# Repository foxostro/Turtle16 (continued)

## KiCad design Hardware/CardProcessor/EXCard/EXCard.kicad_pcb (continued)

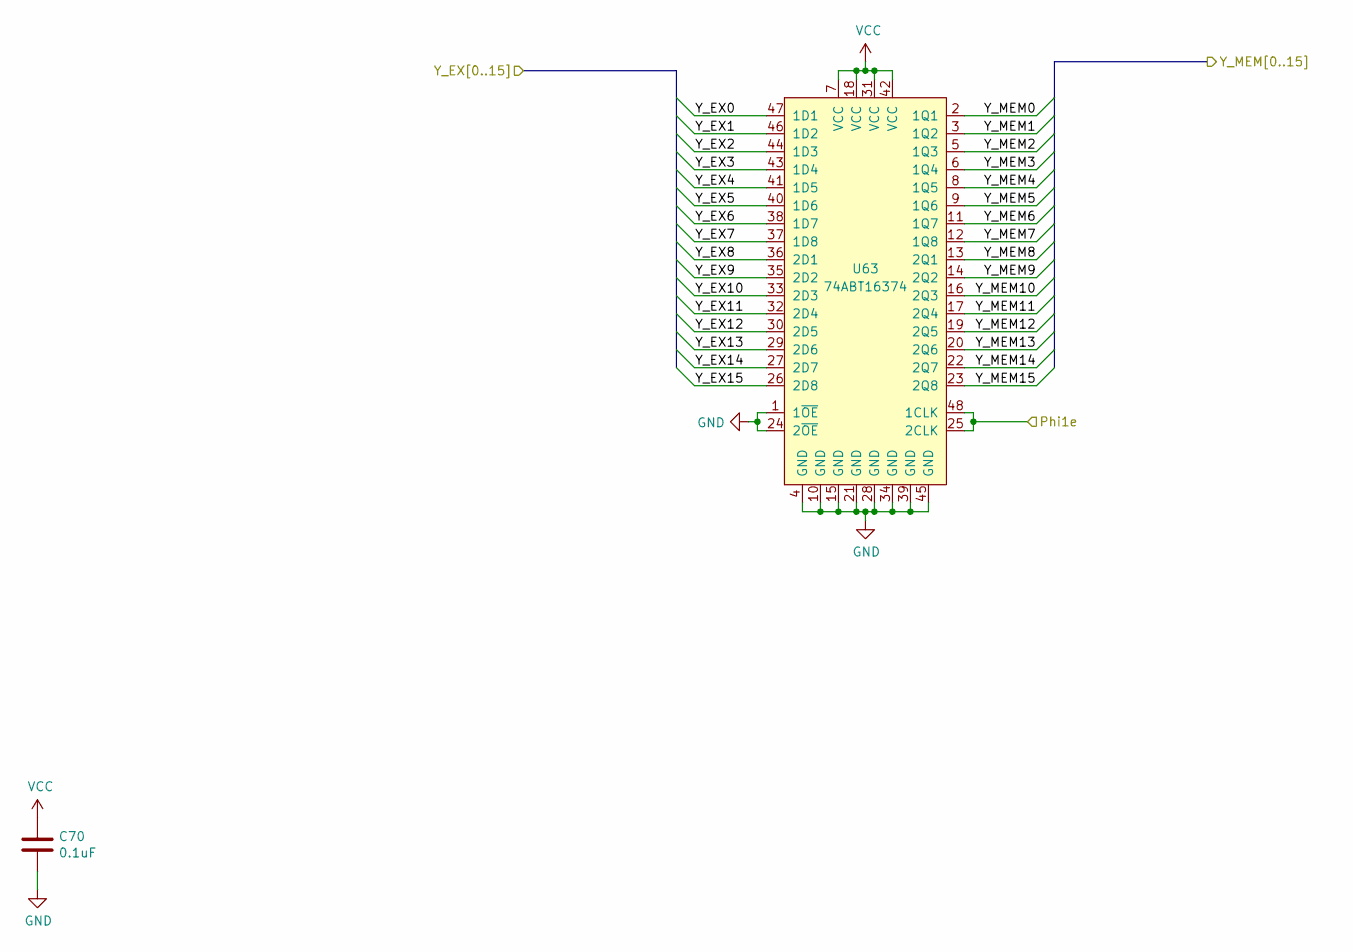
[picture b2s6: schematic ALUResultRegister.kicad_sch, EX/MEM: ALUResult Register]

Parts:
C70: 0.1uF; C_0603_1608Metric; Manufacturer# EMK107B7104KAHT; Digikey# 587-6004-1-ND
U63: 74ABT16374; TSSOP-48_6.1x12.5mm_P0.5mm; Manufacturer# SN74ABT16374ADGGR; Mouser# 595-SNABT16374ADGGR

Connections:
/Phi1e: U63.25 (2CLK), U63.48 (1CLK); also elsewhere on the board
/Y_EX0: U63.47 (1D1); also elsewhere on the board
/Y_EX1: U63.46 (1D2); also elsewhere on the board
/Y_EX2: U63.44 (1D3); also elsewhere on the board
/Y_EX3: U63.43 (1D4); also elsewhere on the board
/Y_EX4: U63.41 (1D5); also elsewhere on the board
/Y_EX5: U63.40 (1D6); also elsewhere on the board
/Y_EX6: U63.38 (1D7); also elsewhere on the board
/Y_EX7: U63.37 (1D8); also elsewhere on the board
/Y_EX8: U63.36 (2D1); also elsewhere on the board
/Y_EX9: U63.35 (2D2); also elsewhere on the board
/Y_EX10: U63.33 (2D3); also elsewhere on the board
/Y_EX11: U63.32 (2D4); also elsewhere on the board
/Y_EX12: U63.30 (2D5); also elsewhere on the board
/Y_EX13: U63.29 (2D6); also elsewhere on the board
/Y_EX14: U63.27 (2D7); also elsewhere on the board
/Y_EX15: U63.26 (2D8); also elsewhere on the board
/Y_MEM0: U63.2 (1Q1); also elsewhere on the board
/Y_MEM1: U63.3 (1Q2); also elsewhere on the board
/Y_MEM2: U63.5 (1Q3); also elsewhere on the board
/Y_MEM3: U63.6 (1Q4); also elsewhere on the board
/Y_MEM4: U63.8 (1Q5); also elsewhere on the board
/Y_MEM5: U63.9 (1Q6); also elsewhere on the board
/Y_MEM6: U63.11 (1Q7); also elsewhere on the board
/Y_MEM7: U63.12 (1Q8); also elsewhere on the board
/Y_MEM8: U63.13 (2Q1); also elsewhere on the board
/Y_MEM9: U63.14 (2Q2); also elsewhere on the board
/Y_MEM10: U63.16 (2Q3); also elsewhere on the board
/Y_MEM11: U63.17 (2Q4); also elsewhere on the board
/Y_MEM12: U63.19 (2Q5); also elsewhere on the board
/Y_MEM13: U63.20 (2Q6); also elsewhere on the board
/Y_MEM14: U63.22 (2Q7); also elsewhere on the board
/Y_MEM15: U63.23 (2Q8); also elsewhere on the board
GND: C70.2, U63.1 (1~OE), U63.4 (GND), U63.10 (GND), U63.15 (GND), U63.21 (GND), U63.24 (2~OE), U63.28 (GND), U63.34 (GND), U63.39 (GND), U63.45 (GND); also elsewhere on the board
VCC: C70.1, U63.7 (VCC), U63.18 (VCC), U63.31 (VCC), U63.42 (VCC); also elsewhere on the board

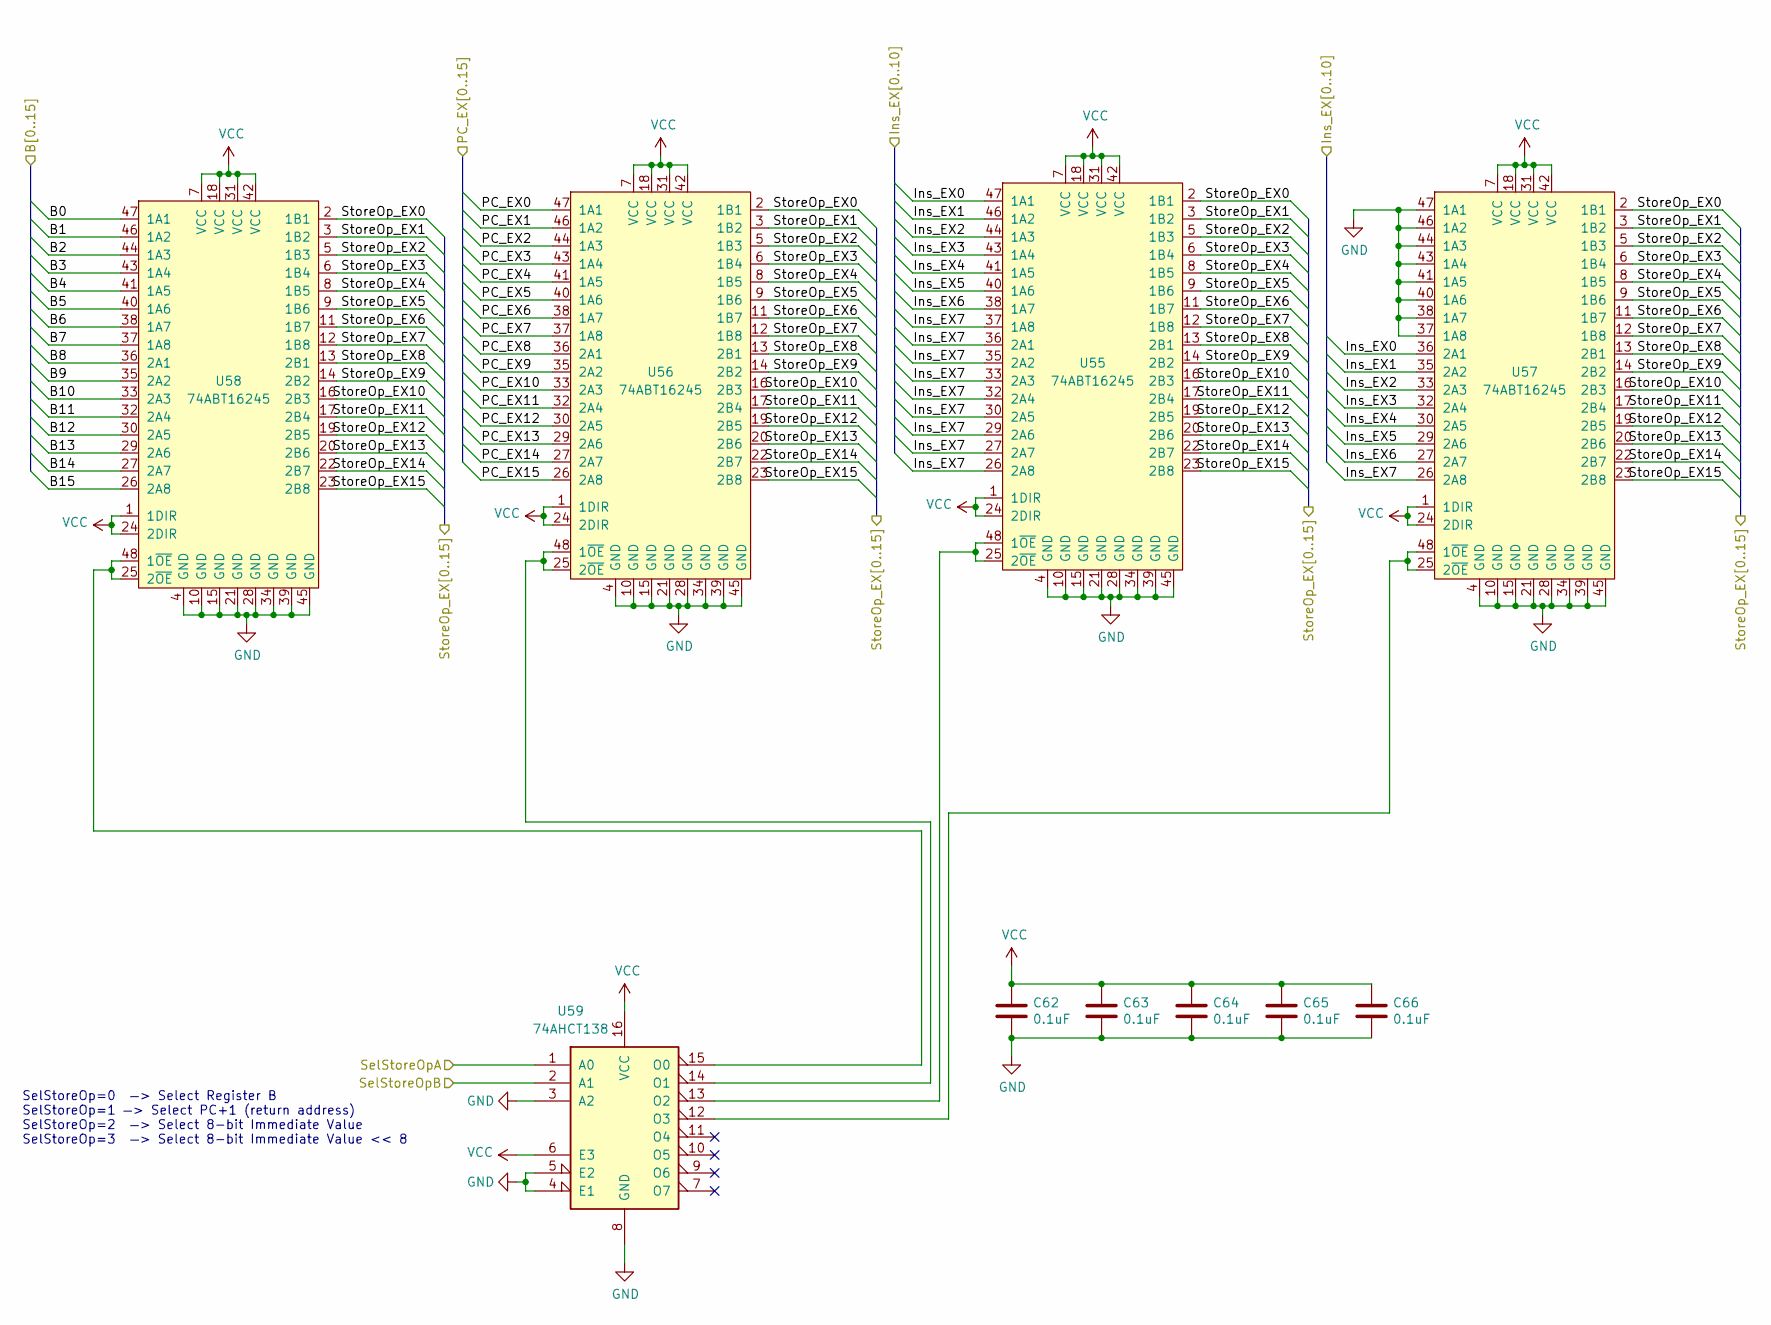
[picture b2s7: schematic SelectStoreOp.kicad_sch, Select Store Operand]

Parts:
C62, C63, C64, C65, C66: 0.1uF; C_0603_1608Metric; Manufacturer# EMK107B7104KAHT; Mouser# 963-EMK107B7104KAHT
U55, U56, U57, U58: 74ABT16245; TSSOP-48_6.1x12.5mm_P0.5mm; Manufacturer# SN74ABTH16245DGGR; Mouser# 595-SNABTH16245DGGR
U59: 74AHCT138; TSSOP-16_4.4x5mm_P0.65mm; Manufacturer# SN74AHCT138PWR; Mouser# 595-SN74AHCT138PWR

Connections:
/B0: U58.47 (1A1); also elsewhere on the board
/B1: U58.46 (1A2); also elsewhere on the board
/B2: U58.44 (1A3); also elsewhere on the board
/B3: U58.43 (1A4); also elsewhere on the board
/B4: U58.41 (1A5); also elsewhere on the board
/B5: U58.40 (1A6); also elsewhere on the board
/B6: U58.38 (1A7); also elsewhere on the board
/B7: U58.37 (1A8); also elsewhere on the board
/B8: U58.36 (2A1); also elsewhere on the board
/B9: U58.35 (2A2); also elsewhere on the board
/B10: U58.33 (2A3); also elsewhere on the board
/B11: U58.32 (2A4); also elsewhere on the board
/B12: U58.30 (2A5); also elsewhere on the board
/B13: U58.29 (2A6); also elsewhere on the board
/B14: U58.27 (2A7); also elsewhere on the board
/B15: U58.26 (2A8); also elsewhere on the board
/Ctl_EX1: U59.1 (A0); also elsewhere on the board
/Ctl_EX2: U59.2 (A1); also elsewhere on the board
/EX/sheet5FD8D6EA/StoreOp_EX0: U55.2 (1B1), U56.2 (1B1), U57.2 (1B1), U58.2 (1B1); also elsewhere on the board
/EX/sheet5FD8D6EA/StoreOp_EX1: U55.3 (1B2), U56.3 (1B2), U57.3 (1B2), U58.3 (1B2); also elsewhere on the board
/EX/sheet5FD8D6EA/StoreOp_EX2: U55.5 (1B3), U56.5 (1B3), U57.5 (1B3), U58.5 (1B3); also elsewhere on the board
/EX/sheet5FD8D6EA/StoreOp_EX3: U55.6 (1B4), U56.6 (1B4), U57.6 (1B4), U58.6 (1B4); also elsewhere on the board
/EX/sheet5FD8D6EA/StoreOp_EX4: U55.8 (1B5), U56.8 (1B5), U57.8 (1B5), U58.8 (1B5); also elsewhere on the board
/EX/sheet5FD8D6EA/StoreOp_EX5: U55.9 (1B6), U56.9 (1B6), U57.9 (1B6), U58.9 (1B6); also elsewhere on the board
/EX/sheet5FD8D6EA/StoreOp_EX6: U55.11 (1B7), U56.11 (1B7), U57.11 (1B7), U58.11 (1B7); also elsewhere on the board
/EX/sheet5FD8D6EA/StoreOp_EX7: U55.12 (1B8), U56.12 (1B8), U57.12 (1B8), U58.12 (1B8); also elsewhere on the board
/EX/sheet5FD8D6EA/StoreOp_EX8: U55.13 (2B1), U56.13 (2B1), U57.13 (2B1), U58.13 (2B1); also elsewhere on the board
/EX/sheet5FD8D6EA/StoreOp_EX9: U55.14 (2B2), U56.14 (2B2), U57.14 (2B2), U58.14 (2B2); also elsewhere on the board
/EX/sheet5FD8D6EA/StoreOp_EX10: U55.16 (2B3), U56.16 (2B3), U57.16 (2B3), U58.16 (2B3); also elsewhere on the board
/EX/sheet5FD8D6EA/StoreOp_EX11: U55.17 (2B4), U56.17 (2B4), U57.17 (2B4), U58.17 (2B4); also elsewhere on the board
/EX/sheet5FD8D6EA/StoreOp_EX12: U55.19 (2B5), U56.19 (2B5), U57.19 (2B5), U58.19 (2B5); also elsewhere on the board
/EX/sheet5FD8D6EA/StoreOp_EX13: U55.20 (2B6), U56.20 (2B6), U57.20 (2B6), U58.20 (2B6); also elsewhere on the board
/EX/sheet5FD8D6EA/StoreOp_EX14: U55.22 (2B7), U56.22 (2B7), U57.22 (2B7), U58.22 (2B7); also elsewhere on the board
/EX/sheet5FD8D6EA/StoreOp_EX15: U55.23 (2B8), U56.23 (2B8), U57.23 (2B8), U58.23 (2B8); also elsewhere on the board
/Ins_EX0: U55.47 (1A1), U57.36 (2A1); also elsewhere on the board
/Ins_EX1: U55.46 (1A2), U57.35 (2A2); also elsewhere on the board
/Ins_EX2: U55.44 (1A3), U57.33 (2A3); also elsewhere on the board
/Ins_EX3: U55.43 (1A4), U57.32 (2A4); also elsewhere on the board
/Ins_EX4: U55.41 (1A5), U57.30 (2A5); also elsewhere on the board
/Ins_EX5: U55.40 (1A6), U57.29 (2A6); also elsewhere on the board
/Ins_EX6: U55.38 (1A7), U57.27 (2A7); also elsewhere on the board
/Ins_EX7: U55.26 (2A8), U55.27 (2A7), U55.29 (2A6), U55.30 (2A5), U55.32 (2A4), U55.33 (2A3), U55.35 (2A2), U55.36 (2A1), U55.37 (1A8), U57.26 (2A8); also elsewhere on the board
/PC_EX0: U56.47 (1A1); also elsewhere on the board
/PC_EX1: U56.46 (1A2); also elsewhere on the board
/PC_EX2: U56.44 (1A3); also elsewhere on the board
/PC_EX3: U56.43 (1A4); also elsewhere on the board
/PC_EX4: U56.41 (1A5); also elsewhere on the board
/PC_EX5: U56.40 (1A6); also elsewhere on the board
/PC_EX6: U56.38 (1A7); also elsewhere on the board
/PC_EX7: U56.37 (1A8); also elsewhere on the board
/PC_EX8: U56.36 (2A1); also elsewhere on the board
/PC_EX9: U56.35 (2A2); also elsewhere on the board
/PC_EX10: U56.33 (2A3); also elsewhere on the board
/PC_EX11: U56.32 (2A4); also elsewhere on the board
/PC_EX12: U56.30 (2A5); also elsewhere on the board
/PC_EX13: U56.29 (2A6); also elsewhere on the board
/PC_EX14: U56.27 (2A7); also elsewhere on the board
/PC_EX15: U56.26 (2A8); also elsewhere on the board
GND: C62.2, C63.2, C64.2, C65.2, C66.2, U55.4 (GND), U55.10 (GND), U55.15 (GND), U55.21 (GND), U55.28 (GND), U55.34 (GND), U55.39 (GND), U55.45 (GND), U56.4 (GND), U56.10 (GND), U56.15 (GND), U56.21 (GND), U56.28 (GND), U56.34 (GND), U56.39 (GND), U56.45 (GND), U57.4 (GND), U57.10 (GND), U57.15 (GND), U57.21 (GND), U57.28 (GND), U57.34 (GND), U57.37 (1A8), U57.38 (1A7), U57.39 (GND), U57.40 (1A6), U57.41 (1A5), U57.43 (1A4), U57.44 (1A3), U57.45 (GND), U57.46 (1A2), U57.47 (1A1), U58.4 (GND), U58.10 (GND), U58.15 (GND), U58.21 (GND), U58.28 (GND), U58.34 (GND), U58.39 (GND), U58.45 (GND), U59.3 (A2), U59.4 (E1), U59.5 (E2), U59.8 (GND); also elsewhere on the board
unnamed: U55.25 (2~OE), U55.48 (1~OE), U59.13 (O2)
unnamed: U56.25 (2~OE), U56.48 (1~OE), U59.14 (O1)
unnamed: U57.25 (2~OE), U57.48 (1~OE), U59.12 (O3)
unnamed: U58.25 (2~OE), U58.48 (1~OE), U59.15 (O0)
VCC: C62.1, C63.1, C64.1, C65.1, C66.1, U55.1 (1DIR), U55.7 (VCC), U55.18 (VCC), U55.24 (2DIR), U55.31 (VCC), U55.42 (VCC), U56.1 (1DIR), U56.7 (VCC), U56.18 (VCC), U56.24 (2DIR), U56.31 (VCC), U56.42 (VCC), U57.1 (1DIR), U57.7 (VCC), U57.18 (VCC), U57.24 (2DIR), U57.31 (VCC), U57.42 (VCC), U58.1 (1DIR), U58.7 (VCC), U58.18 (VCC), U58.24 (2DIR), U58.31 (VCC), U58.42 (VCC), U59.6 (E3), U59.16 (VCC); also elsewhere on the board

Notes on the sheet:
SelStoreOp=0 —> Select Register B SelStoreOp=1 —> Select PC+1 (return address) SelStoreOp=2 —> Select 8-bit Immediate Value SelStoreOp=3 —> Select 8-bit Immediate Value << 8

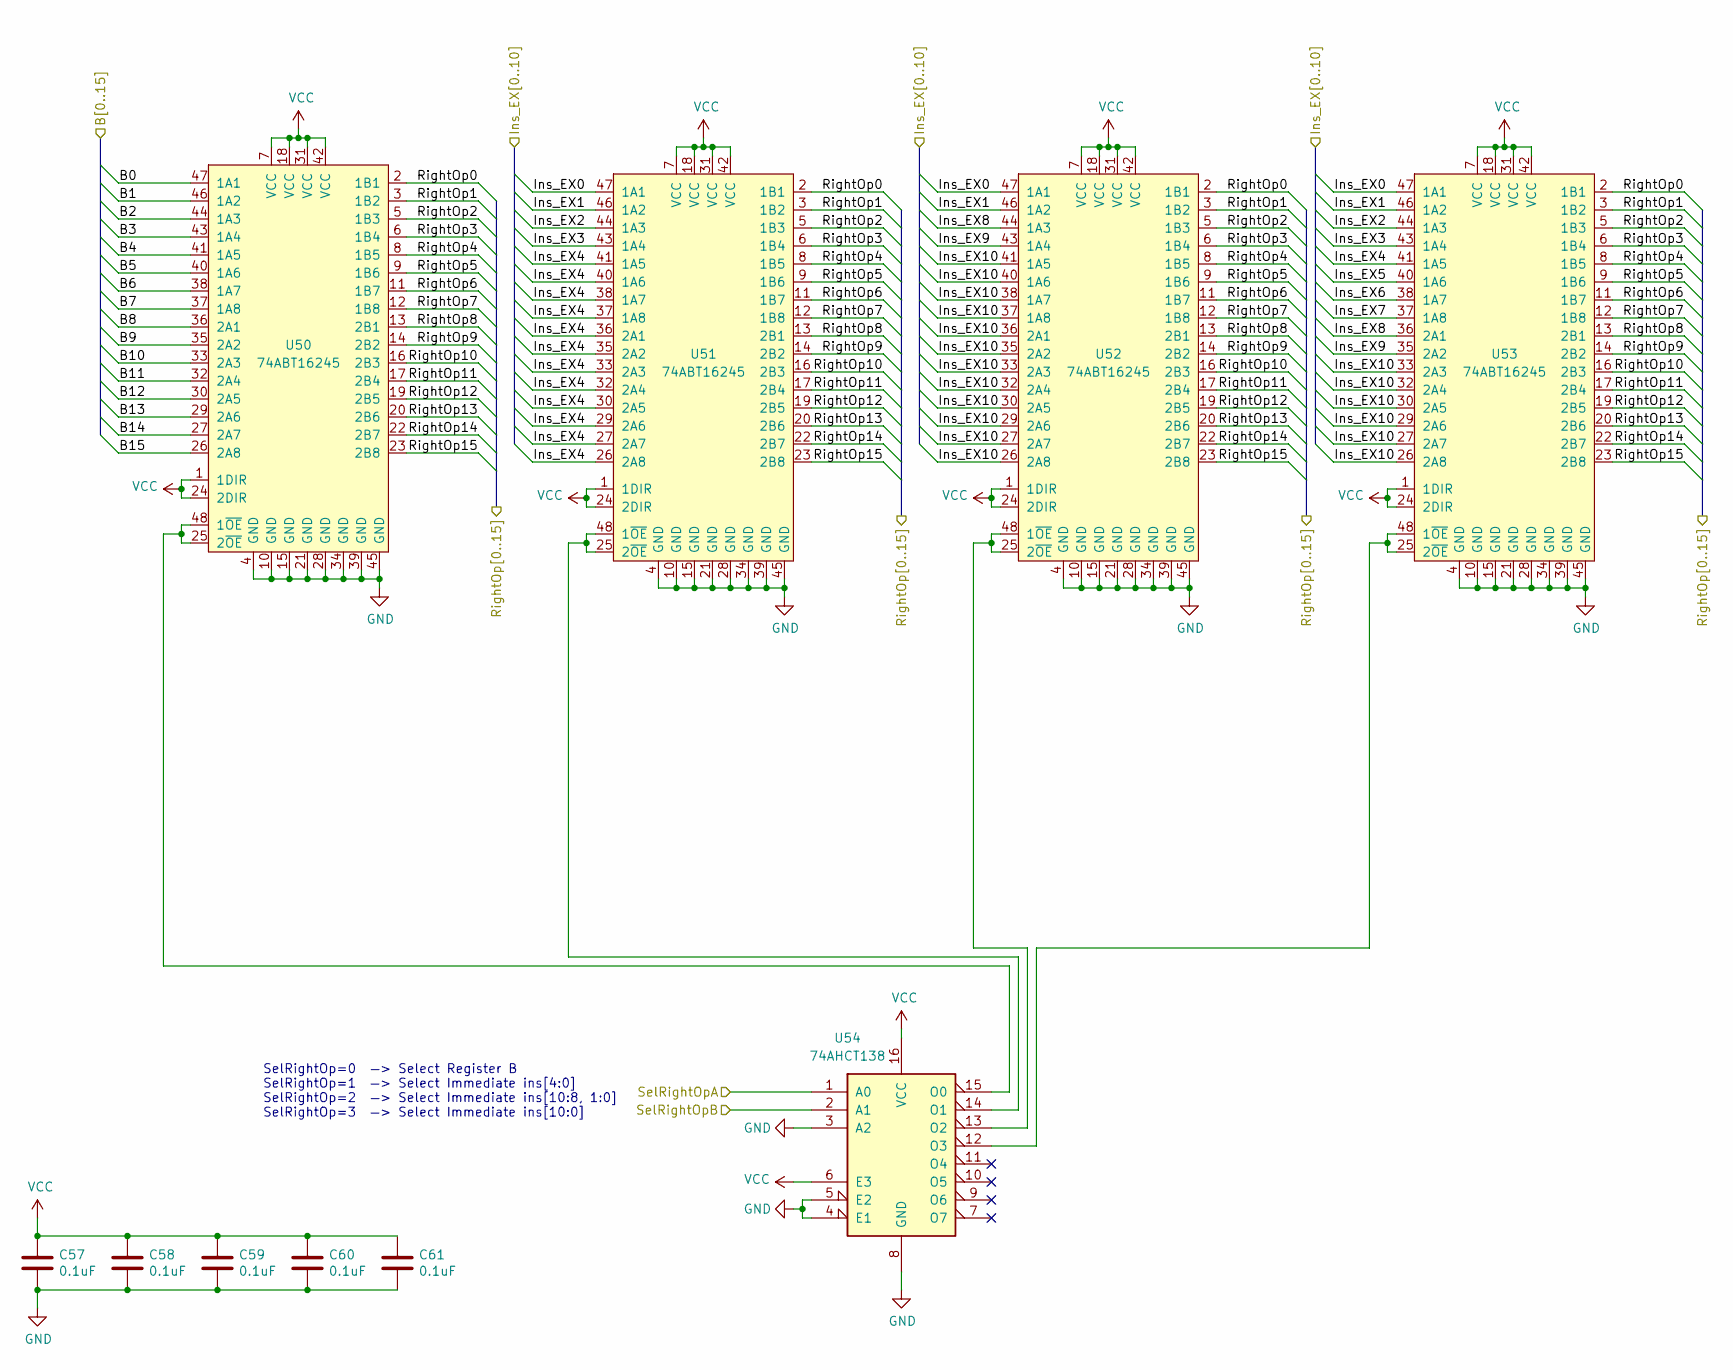
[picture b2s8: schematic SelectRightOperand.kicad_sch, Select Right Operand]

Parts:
C57, C58, C59, C60, C61: 0.1uF; C_0603_1608Metric; Manufacturer# EMK107B7104KAHT; Mouser# 963-EMK107B7104KAHT
U50, U51, U52, U53: 74ABT16245; TSSOP-48_6.1x12.5mm_P0.5mm; Manufacturer# SN74ABTH16245DGGR; Mouser# 595-SNABTH16245DGGR
U54: 74AHCT138; TSSOP-16_4.4x5mm_P0.65mm; Manufacturer# SN74AHCT138PWR; Mouser# 595-SN74AHCT138PWR

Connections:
/B0: U50.47 (1A1); also elsewhere on the board
/B1: U50.46 (1A2); also elsewhere on the board
/B2: U50.44 (1A3); also elsewhere on the board
/B3: U50.43 (1A4); also elsewhere on the board
/B4: U50.41 (1A5); also elsewhere on the board
/B5: U50.40 (1A6); also elsewhere on the board
/B6: U50.38 (1A7); also elsewhere on the board
/B7: U50.37 (1A8); also elsewhere on the board
/B8: U50.36 (2A1); also elsewhere on the board
/B9: U50.35 (2A2); also elsewhere on the board
/B10: U50.33 (2A3); also elsewhere on the board
/B11: U50.32 (2A4); also elsewhere on the board
/B12: U50.30 (2A5); also elsewhere on the board
/B13: U50.29 (2A6); also elsewhere on the board
/B14: U50.27 (2A7); also elsewhere on the board
/B15: U50.26 (2A8); also elsewhere on the board
/Ctl_EX3: U54.1 (A0); also elsewhere on the board
/Ctl_EX4: U54.2 (A1); also elsewhere on the board
/EX/ALU/RightOp0: U50.2 (1B1), U51.2 (1B1), U52.2 (1B1), U53.2 (1B1); also elsewhere on the board
/EX/ALU/RightOp1: U50.3 (1B2), U51.3 (1B2), U52.3 (1B2), U53.3 (1B2); also elsewhere on the board
/EX/ALU/RightOp2: U50.5 (1B3), U51.5 (1B3), U52.5 (1B3), U53.5 (1B3); also elsewhere on the board
/EX/ALU/RightOp3: U50.6 (1B4), U51.6 (1B4), U52.6 (1B4), U53.6 (1B4); also elsewhere on the board
/EX/ALU/RightOp4: U50.8 (1B5), U51.8 (1B5), U52.8 (1B5), U53.8 (1B5); also elsewhere on the board
/EX/ALU/RightOp5: U50.9 (1B6), U51.9 (1B6), U52.9 (1B6), U53.9 (1B6); also elsewhere on the board
/EX/ALU/RightOp6: U50.11 (1B7), U51.11 (1B7), U52.11 (1B7), U53.11 (1B7); also elsewhere on the board
/EX/ALU/RightOp7: U50.12 (1B8), U51.12 (1B8), U52.12 (1B8), U53.12 (1B8); also elsewhere on the board
/EX/ALU/RightOp8: U50.13 (2B1), U51.13 (2B1), U52.13 (2B1), U53.13 (2B1); also elsewhere on the board
/EX/ALU/RightOp9: U50.14 (2B2), U51.14 (2B2), U52.14 (2B2), U53.14 (2B2); also elsewhere on the board
/EX/ALU/RightOp10: U50.16 (2B3), U51.16 (2B3), U52.16 (2B3), U53.16 (2B3); also elsewhere on the board
/EX/ALU/RightOp11: U50.17 (2B4), U51.17 (2B4), U52.17 (2B4), U53.17 (2B4); also elsewhere on the board
/EX/ALU/RightOp12: U50.19 (2B5), U51.19 (2B5), U52.19 (2B5), U53.19 (2B5); also elsewhere on the board
/EX/ALU/RightOp13: U50.20 (2B6), U51.20 (2B6), U52.20 (2B6), U53.20 (2B6); also elsewhere on the board
/EX/ALU/RightOp14: U50.22 (2B7), U51.22 (2B7), U52.22 (2B7), U53.22 (2B7); also elsewhere on the board
/EX/ALU/RightOp15: U50.23 (2B8), U51.23 (2B8), U52.23 (2B8), U53.23 (2B8); also elsewhere on the board
/Ins_EX0: U51.47 (1A1), U52.47 (1A1), U53.47 (1A1); also elsewhere on the board
/Ins_EX1: U51.46 (1A2), U52.46 (1A2), U53.46 (1A2); also elsewhere on the board
/Ins_EX2: U51.44 (1A3), U53.44 (1A3); also elsewhere on the board
/Ins_EX3: U51.43 (1A4), U53.43 (1A4); also elsewhere on the board
/Ins_EX4: U51.26 (2A8), U51.27 (2A7), U51.29 (2A6), U51.30 (2A5), U51.32 (2A4), U51.33 (2A3), U51.35 (2A2), U51.36 (2A1), U51.37 (1A8), U51.38 (1A7), U51.40 (1A6), U51.41 (1A5), U53.41 (1A5); also elsewhere on the board
/Ins_EX5: U53.40 (1A6); also elsewhere on the board
/Ins_EX6: U53.38 (1A7); also elsewhere on the board
/Ins_EX7: U53.37 (1A8); also elsewhere on the board
/Ins_EX8: U52.44 (1A3), U53.36 (2A1); also elsewhere on the board
/Ins_EX9: U52.43 (1A4), U53.35 (2A2); also elsewhere on the board
/Ins_EX10: U52.26 (2A8), U52.27 (2A7), U52.29 (2A6), U52.30 (2A5), U52.32 (2A4), U52.33 (2A3), U52.35 (2A2), U52.36 (2A1), U52.37 (1A8), U52.38 (1A7), U52.40 (1A6), U52.41 (1A5), U53.26 (2A8), U53.27 (2A7), U53.29 (2A6), U53.30 (2A5), U53.32 (2A4), U53.33 (2A3); also elsewhere on the board
GND: C57.2, C58.2, C59.2, C60.2, C61.2, U50.4 (GND), U50.10 (GND), U50.15 (GND), U50.21 (GND), U50.28 (GND), U50.34 (GND), U50.39 (GND), U50.45 (GND), U51.4 (GND), U51.10 (GND), U51.15 (GND), U51.21 (GND), U51.28 (GND), U51.34 (GND), U51.39 (GND), U51.45 (GND), U52.4 (GND), U52.10 (GND), U52.15 (GND), U52.21 (GND), U52.28 (GND), U52.34 (GND), U52.39 (GND), U52.45 (GND), U53.4 (GND), U53.10 (GND), U53.15 (GND), U53.21 (GND), U53.28 (GND), U53.34 (GND), U53.39 (GND), U53.45 (GND), U54.3 (A2), U54.4 (E1), U54.5 (E2), U54.8 (GND); also elsewhere on the board
unnamed: U50.25 (2~OE), U50.48 (1~OE), U54.15 (O0)
unnamed: U51.25 (2~OE), U51.48 (1~OE), U54.14 (O1)
unnamed: U52.25 (2~OE), U52.48 (1~OE), U54.13 (O2)
unnamed: U53.25 (2~OE), U53.48 (1~OE), U54.12 (O3)
VCC: C57.1, C58.1, C59.1, C60.1, C61.1, U50.1 (1DIR), U50.7 (VCC), U50.18 (VCC), U50.24 (2DIR), U50.31 (VCC), U50.42 (VCC), U51.1 (1DIR), U51.7 (VCC), U51.18 (VCC), U51.24 (2DIR), U51.31 (VCC), U51.42 (VCC), U52.1 (1DIR), U52.7 (VCC), U52.18 (VCC), U52.24 (2DIR), U52.31 (VCC), U52.42 (VCC), U53.1 (1DIR), U53.7 (VCC), U53.18 (VCC), U53.24 (2DIR), U53.31 (VCC), U53.42 (VCC), U54.6 (E3), U54.16 (VCC); also elsewhere on the board

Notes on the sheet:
SelRightOp=0 —> Select Register B SelRightOp=1 —> Select Immediate ins[4:0] SelRightOp=2 —> Select Immediate ins[10:8, 1:0] SelRightOp=3 —> Select Immediate ins[10:0]

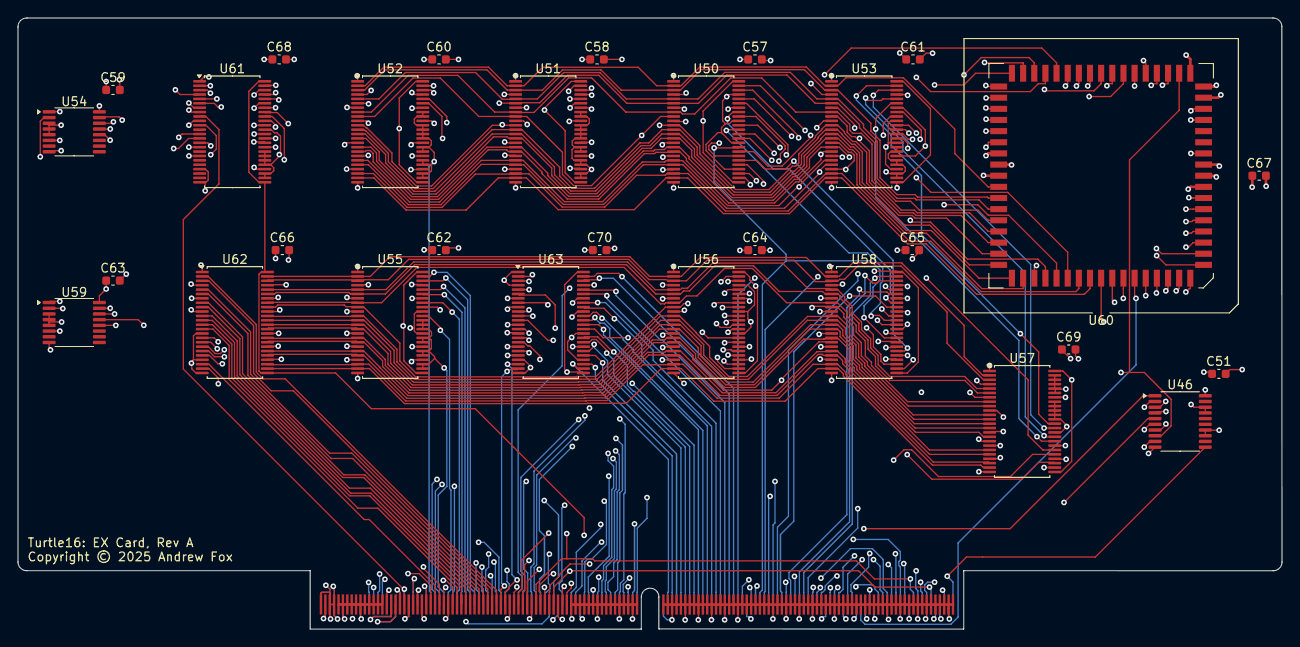
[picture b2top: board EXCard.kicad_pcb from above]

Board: 8 copper layers, 144.0 x 69.6 mm, 31 parts (0 on the bottom side), 185 nets.

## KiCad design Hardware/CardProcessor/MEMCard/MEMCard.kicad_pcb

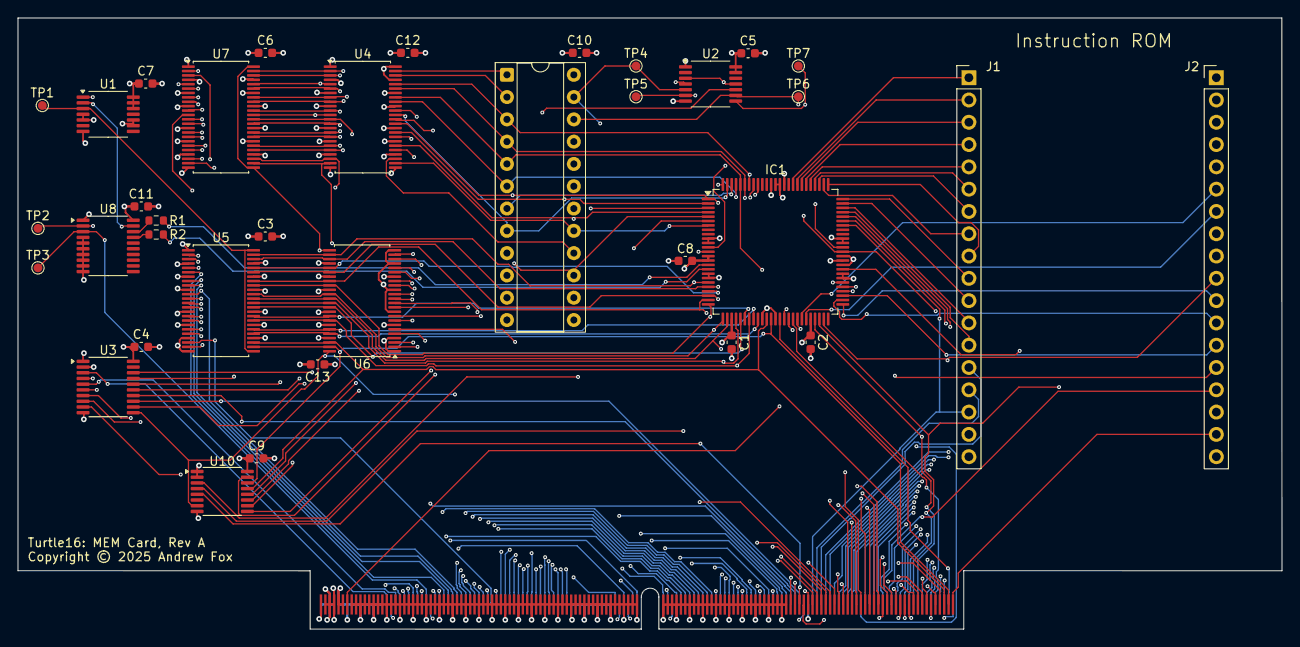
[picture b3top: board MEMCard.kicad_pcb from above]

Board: 6 copper layers, 144.0 x 69.6 mm, 36 parts (0 on the bottom side), 165 nets.

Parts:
C1, C2, C3, C4, C5, C6, C7, C8, C9, C10, C11, C12, C13: 0.1uF; C_0603_1608Metric
IC1: 7028L20PFGI; TQFP-100_14x14mm_P0.5mm
J1: UpperHeader; PinHeader_1x18_P2.54mm_Vertical
J2: LowerHeader; PinHeader_1x18_P2.54mm_Vertical
J3: MEC5-140-01-L-DV-W1-K; MEC5-140-01-L-DV-W1-K_Edge
R1, R2: 0R; R_0603_1608Metric
TP1: ~{AssertData}; TestPoint_Pad_D1.0mm
TP2: ~{MemStoreIn}; TestPoint_Pad_D1.0mm
TP3: ~{MemLoadIn}; TestPoint_Pad_D1.0mm
TP4, TP5, TP6, TP7: TestPoint; TestPoint_Pad_D1.0mm
U1: 74ABT32; TSSOP-14_4.4x5mm_P0.65mm
U2: 74AHCT04; TSSOP-14_4.4x5mm_P0.65mm
U3: 74ABT574; TSSOP-20_4.4x6.5mm_P0.65mm
U4, U5: 74ABT16245; TSSOP-48_6.1x12.5mm_P0.5mm
U6, U7: 74ABT16374; TSSOP-48_6.1x12.5mm_P0.5mm
U8: 74ABT245; TSSOP-20_4.4x6.5mm_P0.65mm
U9: ATF22V10C-7PX; DIP-24_W7.62mm_Socket
U10: CD74HC173PWR; TSSOP-16_4.4x5mm_P0.65mm

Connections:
/Addr0: IC1.92 (A0L), J3.245, U4.47 (1A1), U9.1 (IN/CLK)
/Addr1: IC1.93 (A1L), J3.243, U4.46 (1A2), U9.2 (IN)
/Addr2: IC1.94 (A2L), J3.241, U4.44 (1A3), U9.3 (IN)
/Addr3: IC1.95 (A3L), J3.239, U4.43 (1A4), U9.4 (IN)
/Addr4: IC1.96 (A4L), J3.237, U4.41 (1A5), U9.5 (IN)
/Addr5: IC1.97 (A5L), J3.235, U4.40 (1A6), U9.6 (IN)
/Addr6: IC1.98 (A6L), J3.233, U4.38 (1A7), U9.7 (IN)
/Addr7: IC1.99 (A7L), J3.231, U4.37 (1A8), U9.8 (IN)
/Addr8: IC1.100 (A8L), J3.229, U4.36 (2A1), U9.9 (IN)
/Addr9: IC1.1 (A9L), J3.227, U4.35 (2A2), U9.10 (IN)
/Addr10: IC1.2 (A10L), J3.225, U4.33 (2A3), U9.11 (IN)
/Addr11: IC1.3 (A11L), J3.223, U4.32 (2A4), U9.13 (IN/~OE)
/Addr12: IC1.4 (A12L), J3.221, U4.30 (2A5), U9.14 (I/O)
/Addr13: IC1.5 (A13L), J3.219, U4.29 (2A6), U9.15 (I/O)
/Addr14: IC1.6 (A14L), J3.217, U4.27 (2A7), U9.16 (I/O)
/Addr15: IC1.7 (A15L), J3.215, U4.26 (2A8), U9.17 (I/O)
/Bank0: J3.213, U9.18 (I/O), U10.3 (Q0)
/Bank1: J3.211, U9.19 (I/O), U10.4 (Q1)
/Bank2: J3.209, U9.20 (I/O), U10.5 (Q2)
/Ctl_MEM14: J3.50, TP3.1, U8.3 (A1)
/Ctl_MEM15: J3.48, TP2.1, U8.2 (A0)
/Ctl_MEM16: J3.46, U1.1
/Ctl_MEM17: J3.44, U3.9 (D7)
/Ctl_MEM18: J3.42, U3.8 (D6)
/Ctl_MEM19: J3.40, U3.7 (D5)
/Ctl_MEM20: J3.38, U3.6 (D4)
/Ctl_WB17: J3.212, U3.12 (Q7)
/Ctl_WB18: J3.210, U3.13 (Q6)
/Ctl_WB19: J3.208, U3.14 (Q5)
/Ctl_WB20: J3.206, U3.15 (Q4)
/FLUSH_IF: IC1.59 (~OER), J2.17, J3.279
/IO0: IC1.37 (I/O0L), J3.277, U5.26 (2A8), U6.47 (1D1), U10.14 (D0)
/IO1: IC1.36 (I/O1L), J3.275, U5.27 (2A7), U6.46 (1D2), U10.13 (D1)
/IO2: IC1.34 (I/O2L), J3.273, U5.29 (2A6), U6.44 (1D3), U10.12 (D2)
/IO3: IC1.33 (I/O3L), J3.271, U5.30 (2A5), U6.43 (1D4), U10.11 (D3)
/IO4: IC1.32 (I/O4L), J3.269, U5.32 (2A4), U6.41 (1D5)
/IO5: IC1.31 (I/O5L), J3.267, U5.33 (2A3), U6.40 (1D6)
/IO6: IC1.30 (I/O6L), J3.265, U5.35 (2A2), U6.38 (1D7)
/IO7: IC1.29 (I/O7L), J3.263, U5.36 (2A1), U6.37 (1D8)
/IO8: IC1.27 (I/O8L), J3.261, U5.37 (1A8), U6.36 (2D1)
/IO9: IC1.26 (I/O9L), J3.259, U5.38 (1A7), U6.35 (2D2)
/IO10: IC1.25 (I/O10L), J3.257, U5.40 (1A6), U6.33 (2D3)
/IO11: IC1.24 (I/O11L), J3.255, U5.41 (1A5), U6.32 (2D4)
/IO12: IC1.23 (I/O12L), J3.253, U5.43 (1A4), U6.30 (2D5)
/IO13: IC1.22 (I/O13L), J3.251, U5.44 (1A3), U6.29 (2D6)
/IO14: IC1.21 (I/O14L), J3.249, U5.46 (1A2), U6.27 (2D7)
/IO15: IC1.20 (I/O15L), J3.247, U5.47 (1A1), U6.26 (2D8)
/Ins_IF0: IC1.39 (I/O0R), J2.1, J3.278
/Ins_IF1: IC1.40 (I/O1R), J2.2, J3.276
/Ins_IF2: IC1.41 (I/O2R), J2.3, J3.274
/Ins_IF3: IC1.42 (I/O3R), J2.4, J3.272
/Ins_IF4: IC1.43 (I/O4R), J2.5, J3.270
/Ins_IF5: IC1.44 (I/O5R), J2.6, J3.268
/Ins_IF6: IC1.45 (I/O6R), J2.7, J3.266
/Ins_IF7: IC1.47 (I/O7R), J2.8, J3.264
/Ins_IF8: IC1.48 (I/O8R), J2.9, J3.262
/Ins_IF9: IC1.49 (I/O9R), J2.10, J3.260
/Ins_IF10: IC1.51 (I/O10R), J2.11, J3.258
/Ins_IF11: IC1.52 (I/O11R), J2.12, J3.256
/Ins_IF12: IC1.53 (I/O12R), J2.13, J3.254
/Ins_IF13: IC1.54 (I/O13R), J2.14, J3.252
/Ins_IF14: IC1.55 (I/O14R), J2.15, J3.250
/Ins_IF15: IC1.56 (I/O15R), J2.16, J3.248
/MEMModule/MEM/Buffer StoreOp As Bus I/O/~AssertData: TP1.1, U1.3, U5.25 (2~OE), U5.48 (1~OE)
/MEMModule/MEM/~AssertCtl: U1.2, U2.4, U8.19 (CE)
/MEMModule/Memory/RAMEN_L: IC1.13 (CE1L), TP4.1, U2.5, U9.23 (I/O)
/MEMModule/Memory/RAMEN_R: IC1.63 (CE1R), J2.18, TP6.1, U2.9, U9.22 (I/O)
/MEMModule/Memory/~RAMEN_L: IC1.12 (~CE0L), TP5.1, U2.6
/MEMModule/Memory/~RAMEN_R: IC1.64 (~CE0R), TP7.1, U2.8
/PC0: IC1.84 (A0R), J1.1, J3.246
/PC1: IC1.83 (A1R), J1.2, J3.244
/PC2: IC1.82 (A2R), J1.3, J3.242
/PC3: IC1.81 (A3R), J1.4, J3.240
/PC4: IC1.80 (A4R), J1.5, J3.238
/PC5: IC1.79 (A5R), J1.6, J3.236
/PC6: IC1.78 (A6R), J1.7, J3.234
/PC7: IC1.77 (A7R), J1.8, J3.232
/PC8: IC1.76 (A8R), J1.9, J3.230
/PC9: IC1.75 (A9R), J1.10, J3.228
/PC10: IC1.74 (A10R), J1.11, J3.226
/PC11: IC1.73 (A11R), J1.12, J3.224
/PC12: IC1.72 (A12R), J1.13, J3.222
/PC13: IC1.71 (A13R), J1.14, J3.220
/PC14: IC1.70 (A14R), J1.15, J3.218
/PC15: IC1.69 (A15R), J1.16, J3.216
/Phi1b: J3.280, U3.11 (Cp), U6.25 (2CLK), U6.48 (1CLK), U7.25 (2CLK), U7.48 (1CLK), U10.7 (Cp)
/SelC_MEM0: J3.36, U3.5 (D3)
/SelC_MEM1: J3.34, U3.4 (D2)
/SelC_MEM2: J3.32, U3.3 (D1)
/SelC_WB0: J3.140, U3.16 (Q3)
/SelC_WB1: J3.138, U3.17 (Q2)
/SelC_WB2: J3.136, U3.18 (Q1)
/StoreOp_MEM0: J3.82, U5.23 (2B8)
/StoreOp_MEM1: J3.80, U5.22 (2B7)
/StoreOp_MEM2: J3.78, U5.20 (2B6)
/StoreOp_MEM3: J3.76, U5.19 (2B5)
/StoreOp_MEM4: J3.74, U5.17 (2B4)
/StoreOp_MEM5: J3.72, U5.16 (2B3)
/StoreOp_MEM6: J3.70, U5.14 (2B2)
/StoreOp_MEM7: J3.68, U5.13 (2B1)
/StoreOp_MEM8: J3.66, U5.12 (1B8)
/StoreOp_MEM9: J3.64, U5.11 (1B7)
/StoreOp_MEM10: J3.62, U5.9 (1B6)
/StoreOp_MEM11: J3.60, U5.8 (1B5)
/StoreOp_MEM12: J3.58, U5.6 (1B4)
/StoreOp_MEM13: J3.56, U5.5 (1B3)
/StoreOp_MEM14: J3.54, U5.3 (1B2)
/StoreOp_MEM15: J3.52, U5.2 (1B1)
/StoreOp_WB0: J3.204, U6.2 (1Q1)
/StoreOp_WB1: J3.202, U6.3 (1Q2)
/StoreOp_WB2: J3.200, U6.5 (1Q3)
/StoreOp_WB3: J3.198, U6.6 (1Q4)
/StoreOp_WB4: J3.196, U6.8 (1Q5)
/StoreOp_WB5: J3.194, U6.9 (1Q6)
/StoreOp_WB6: J3.192, U6.11 (1Q7)
/StoreOp_WB7: J3.190, U6.12 (1Q8)
/StoreOp_WB8: J3.188, U6.13 (2Q1)
/StoreOp_WB9: J3.186, U6.14 (2Q2)
/StoreOp_WB10: J3.184, U6.16 (2Q3)
/StoreOp_WB11: J3.182, U6.17 (2Q4)
/StoreOp_WB12: J3.180, U6.19 (2Q5)
/StoreOp_WB13: J3.178, U6.20 (2Q6)
/StoreOp_WB14: J3.176, U6.22 (2Q7)
/StoreOp_WB15: J3.174, U6.23 (2Q8)
/Y_MEM0: J3.114, U4.2 (1B1), U7.47 (1D1)
/Y_MEM1: J3.112, U4.3 (1B2), U7.46 (1D2)
/Y_MEM2: J3.110, U4.5 (1B3), U7.44 (1D3)
/Y_MEM3: J3.108, U4.6 (1B4), U7.43 (1D4)
/Y_MEM4: J3.106, U4.8 (1B5), U7.41 (1D5)
/Y_MEM5: J3.104, U4.9 (1B6), U7.40 (1D6)
/Y_MEM6: J3.102, U4.11 (1B7), U7.38 (1D7)
/Y_MEM7: J3.100, U4.12 (1B8), U7.37 (1D8)
/Y_MEM8: J3.98, U4.13 (2B1), U7.36 (2D1)
/Y_MEM9: J3.96, U4.14 (2B2), U7.35 (2D2)
/Y_MEM10: J3.94, U4.16 (2B3), U7.33 (2D3)
/Y_MEM11: J3.92, U4.17 (2B4), U7.32 (2D4)
/Y_MEM12: J3.90, U4.19 (2B5), U7.30 (2D5)
/Y_MEM13: J3.88, U4.20 (2B6), U7.29 (2D6)
/Y_MEM14: J3.86, U4.22 (2B7), U7.27 (2D7)
/Y_MEM15: J3.84, U4.23 (2B8), U7.26 (2D8)
/Y_WB0: J3.142, U7.2 (1Q1)
/Y_WB1: J3.144, U7.3 (1Q2)
/Y_WB2: J3.146, U7.5 (1Q3)
/Y_WB3: J3.148, U7.6 (1Q4)
/Y_WB4: J3.150, U7.8 (1Q5)
/Y_WB5: J3.152, U7.9 (1Q6)
/Y_WB6: J3.154, U7.11 (1Q7)
/Y_WB7: J3.156, U7.12 (1Q8)
/Y_WB8: J3.158, U7.13 (2Q1)
/Y_WB9: J3.160, U7.14 (2Q2)
/Y_WB10: J3.162, U7.16 (2Q3)
/Y_WB11: J3.164, U7.17 (2Q4)
/Y_WB12: J3.166, U7.19 (2Q5)
/Y_WB13: J3.168, U7.20 (2Q6)
/Y_WB14: J3.170, U7.22 (2Q7)
/Y_WB15: J3.172, U7.23 (2Q8)
/~MemLoad: IC1.17 (~OEL), J3.205, R2.2
/~MemStore: IC1.16 (R/~WL), J3.207, R1.2, U10.10 (E2)
/~RST_sync: J3.13, U2.3, U2.11
GND: C1.2, C2.2, C3.2, C4.2, C5.2, C6.2, C7.2, C8.2, C9.2, C10.2, C11.2, C12.2, C13.2, IC1.10 (~LBL), IC1.11 (~UBL), IC1.18 (GND_1), IC1.19 (GND_2), IC1.35 (GND_3), IC1.38 (GND_4), IC1.57 (GND_5), IC1.58 (GND_6), IC1.61 (GND_7), IC1.65 (~UBR), IC1.66 (~LBR), IC1.87 (M/~S), IC1.88 (GND_8), J1.17, J3.1, J3.2, J3.4, J3.9, J3.10, J3.11, J3.12, J3.14, J3.15, J3.16, J3.17, J3.18, J3.19, J3.20, J3.21, J3.22, J3.23, J3.24, J3.25, J3.26, J3.27, J3.28, J3.29, J3.30, J3.31, J3.33, J3.35, J3.37, J3.39, J3.41, J3.43, J3.45, J3.47, J3.49, J3.51, J3.53, J3.55, J3.57, J3.59, J3.61, J3.63, J3.65, J3.67, J3.69, J3.71, J3.73, J3.75, J3.77, J3.79, J3.81, J3.83, J3.85, J3.87, J3.89, J3.91, J3.93, J3.95, J3.97, J3.99, J3.101, J3.103, J3.105, J3.107, J3.109, J3.111, J3.113, J3.115, J3.116, J3.117, J3.118, J3.119, J3.120, J3.121, J3.122, J3.123, J3.124, J3.125, J3.126, J3.127, J3.128, J3.129, J3.130, J3.131, J3.132, J3.133, J3.134, J3.135, J3.137, J3.139, J3.141, J3.143, J3.145, J3.147, J3.149, J3.151, J3.153, J3.155, J3.157, J3.159, J3.161, J3.163, J3.165, J3.167, J3.169, J3.171, J3.173, J3.175, J3.177, J3.179, J3.181, J3.183, J3.185, J3.187, J3.189, J3.191, J3.193, J3.195, J3.197, J3.199, J3.201, J3.203, J3.214, U1.7 (GND), U2.7 (GND), U3.1 (OE), U3.10 (GND), U4.1 (1DIR), U4.4 (GND), U4.10 (GND), U4.15 (GND), U4.21 (GND), U4.24 (2DIR), U4.25 (2~OE), U4.28 (GND), U4.34 (GND), U4.39 (GND), U4.45 (GND), U4.48 (1~OE), U5.1 (1DIR), U5.4 (GND), U5.10 (GND), U5.15 (GND), U5.21 (GND), U5.24 (2DIR), U5.28 (GND), U5.34 (GND), U5.39 (GND), U5.45 (GND), U6.1 (1~OE), U6.4 (GND), U6.10 (GND), U6.15 (GND), U6.21 (GND), U6.24 (2~OE), U6.28 (GND), U6.34 (GND), U6.39 (GND), U6.45 (GND), U7.1 (1~OE), U7.4 (GND), U7.10 (GND), U7.15 (GND), U7.21 (GND), U7.24 (2~OE), U7.28 (GND), U7.34 (GND), U7.39 (GND), U7.45 (GND), U8.4 (A2), U8.5 (A3), U8.6 (A4), U8.7 (A5), U8.8 (A6), U8.9 (A7), U8.10 (GND), U9.12 (GND), U10.1 (Oe1), U10.2 (Oe2), U10.8 (GND)
unnamed: R1.1, U8.18 (B0)
unnamed: R2.1, U8.17 (B1)
unnamed: U9.21 (I/O), U10.9 (E1)
unnamed: U2.10, U10.15 (Mr)
VCC: C1.1, C2.1, C3.1, C4.1, C5.1, C6.1, C7.1, C8.1, C9.1, C10.1, C11.1, C12.1, C13.1, IC1.14 (~SEML), IC1.15 (VCC_1), IC1.28 (VCC_2), IC1.46 (VCC_3), IC1.60 (R/~WR), IC1.62 (~SEMR), IC1.86 (~BUSYR), IC1.89 (~BUSYL), J1.18, J3.3, J3.5, J3.6, J3.7, J3.8, U1.4, U1.5, U1.9, U1.10, U1.12, U1.13, U1.14 (VCC), U2.1, U2.13, U2.14 (VCC), U3.2 (D0), U3.20 (VCC), U4.7 (VCC), U4.18 (VCC), U4.31 (VCC), U4.42 (VCC), U5.7 (VCC), U5.18 (VCC), U5.31 (VCC), U5.42 (VCC), U6.7 (VCC), U6.18 (VCC), U6.31 (VCC), U6.42 (VCC), U7.7 (VCC), U7.18 (VCC), U7.31 (VCC), U7.42 (VCC), U8.1 (A->B), U8.20 (VCC), U9.24 (VCC), U10.16 (VCC)

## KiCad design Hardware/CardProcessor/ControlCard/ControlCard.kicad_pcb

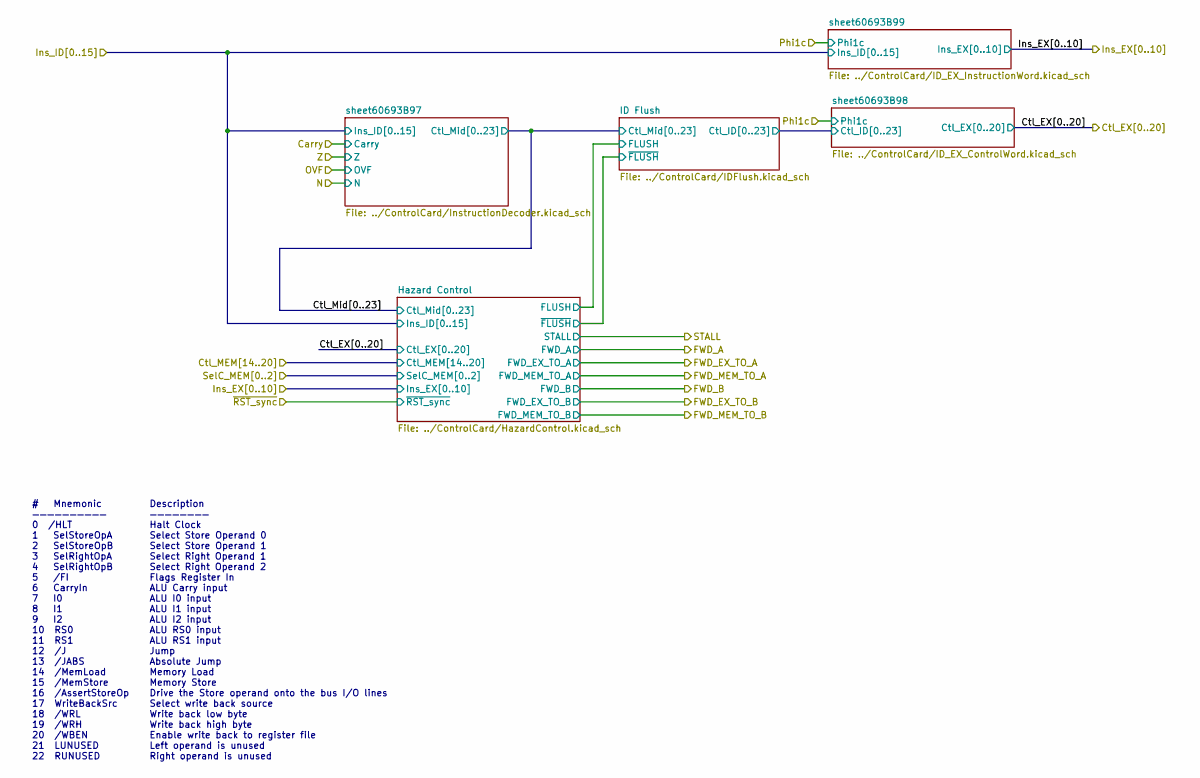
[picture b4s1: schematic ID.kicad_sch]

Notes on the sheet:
Description ———————— Halt Clock Select Store Operand 0 Select Store Operand 1 Select Right Operand 1 Select Right Operand 2 Flags Register In ALU Carry input ALU I0 input ALU I1 input ALU I2 input ALU RS0 input ALU RS1 input Jump Absolute Jump Memory Load Memory Store Drive the Store operand onto t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
# Mnemonic —————————— 0 /HLT 1 SelStoreOpA 2 SelStoreOpB 3 SelRightOpA 4 SelRightOpB 5 /FI 6 CarryIn 7 I0 8 I1 9 I2 10 RS0 11 RS1 12 /J 13 /JABS 14 /MemLoad 15 /MemStore 16 /AssertStoreOp 17 WriteBackSrc 18 /WRL 19 /WRH 20 /WBEN 21 LUNUSED 22 RUNUSED
